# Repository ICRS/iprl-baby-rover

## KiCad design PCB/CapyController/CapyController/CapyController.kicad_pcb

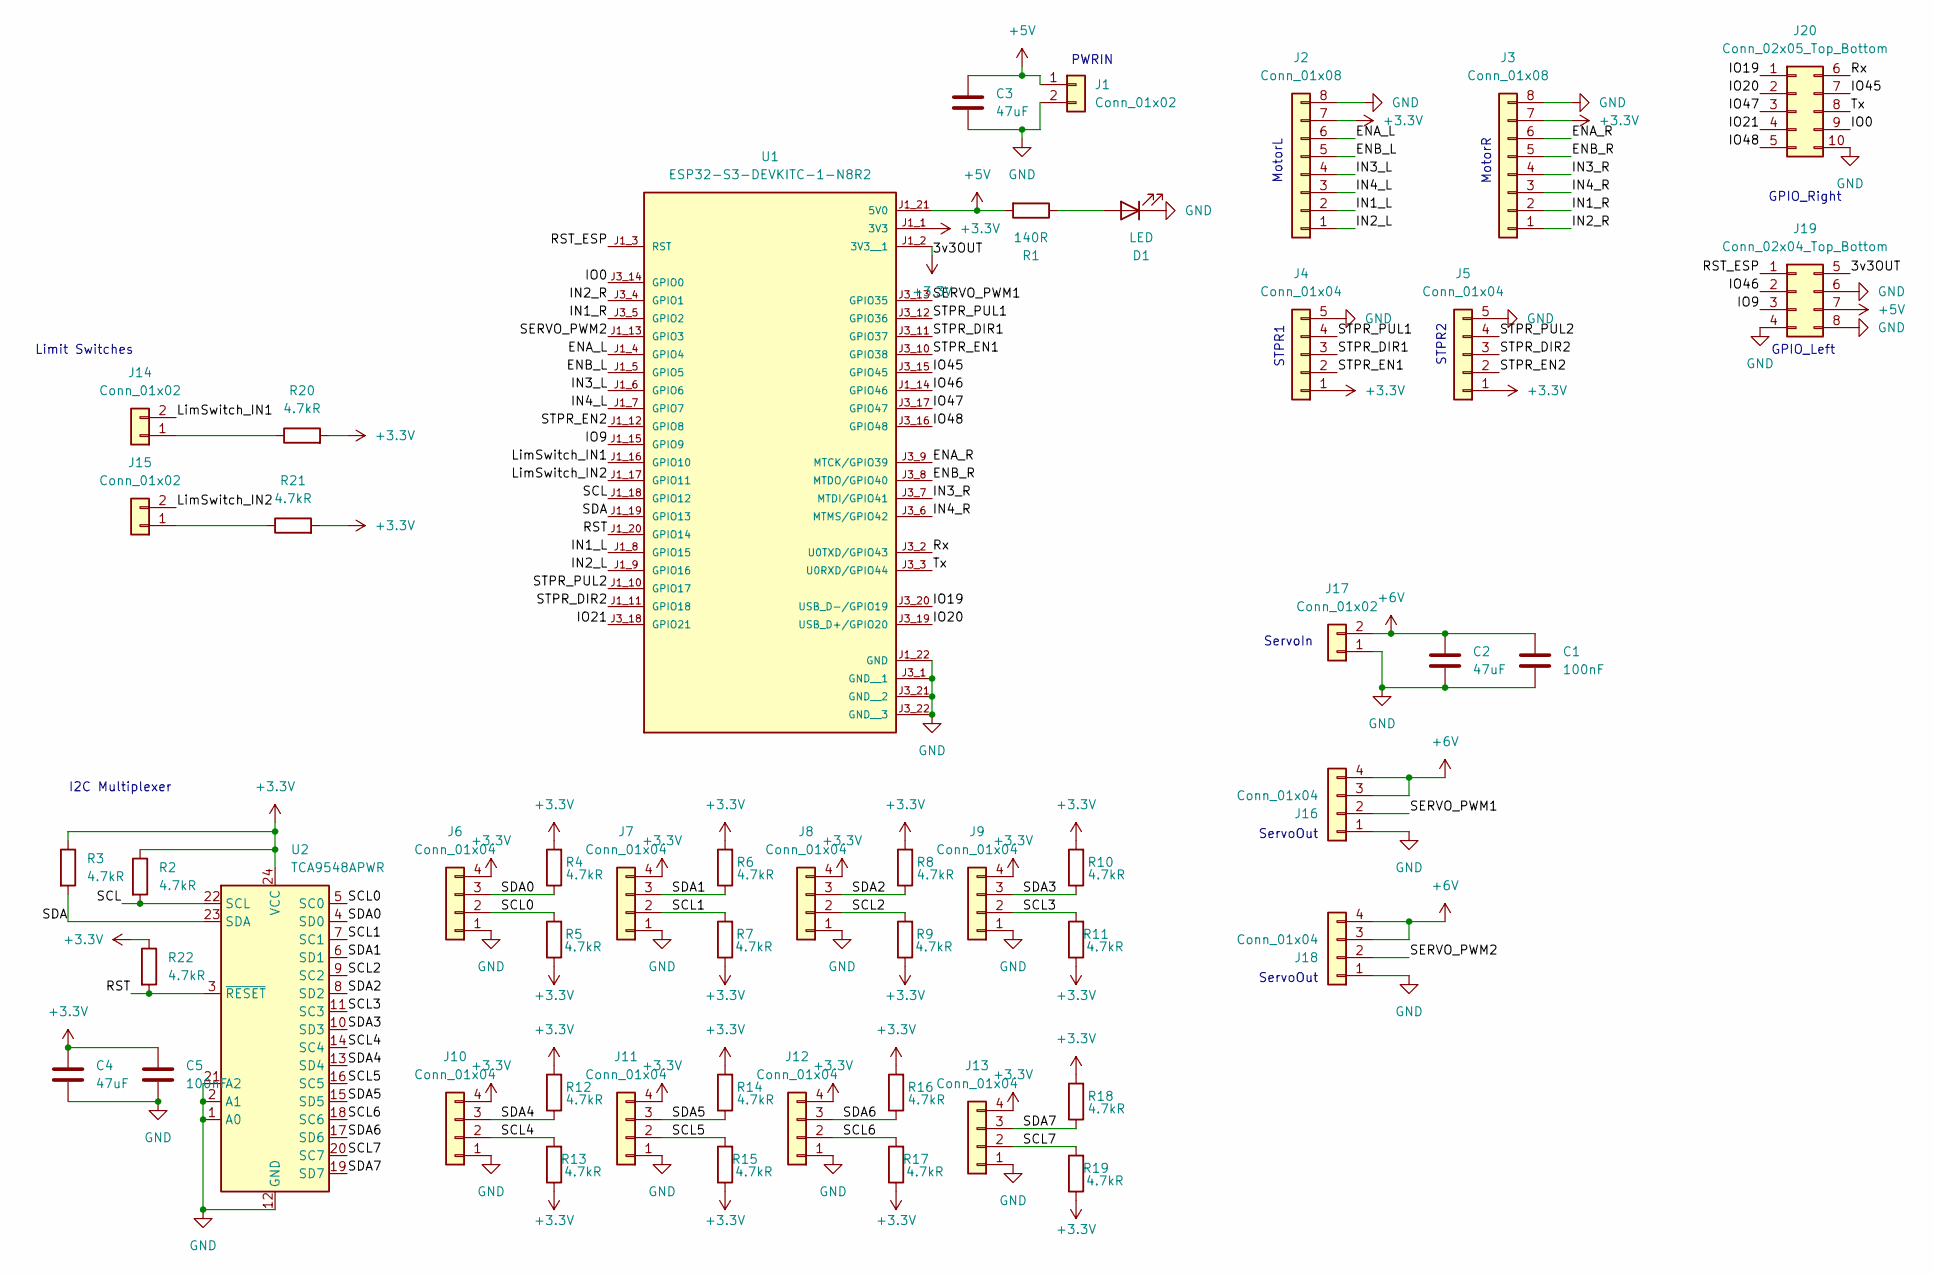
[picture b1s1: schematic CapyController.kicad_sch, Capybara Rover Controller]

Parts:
C1, C5: 100nF; C_1206_3216Metric
C2, C3, C4: 47uF; C_1206_3216Metric
D1: LED; LED_0402_1005Metric
J1, J14, J15, J17: Conn_01x02; TerminalBlock_WAGO_233-502_2x02_P2.54mm
J2, J3: Conn_01x08; JST_PH_B8B-PH-K_1x08_P2.00mm_Vertical
J4, J5: Conn_01x04; JST_PH_B5B-PH-K_1x05_P2.00mm_Vertical
J6, J7, J8, J9, J10, J11, J12, J13: Conn_01x04; JST_PH_B4B-PH-K_1x04_P2.00mm_Vertical
J16, J18: Conn_01x04; TerminalBlock_WAGO_233-504_2x04_P2.54mm
J19: Conn_02x04_Top_Bottom; PinHeader_2x04_P2.54mm_Vertical
J20: Conn_02x05_Top_Bottom; PinSocket_2x05_P2.54mm_Vertical
R1: 140R; R_0402_1005Metric
R2, R3, R4, R5, R6, R7, R8, R9, R10, R11, R12, R13, R14, R15, R16, R17, R18, R19, R20, R21, R22: 4.7kR; R_0402_1005Metric
U1: ESP32-S3-DEVKITC-1-N8R2; XCVR_ESP32-S3-DEVKITC-1-N8R2; PARTREV V1
U2: TCA9548APWR; TSSOP-24_4.4x7.8mm_P0.65mm

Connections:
+3.3V: C4.2, C5.2, J2.7, J3.7, J4.1, J5.1, J6.4, J7.4, J8.4, J9.4, J10.4, J11.4, J12.4, J13.4, J19.5, R2.1, R3.1, R4.2, R5.1, R6.2, R7.1, R8.2, R9.1, R10.2, R11.1, R12.2, R13.1, R14.2, R15.1, R16.2, R17.1, R18.2, R19.1, R20.2, R21.2, R22.1, U1.J1_1 (3V3), U1.J1_2 (3V3__1), U2.24 (VCC)
+5V: C3.2, J1.1, J19.7, R1.2, U1.J1_21 (5V0)
+6V: C1.2, C2.2, J16.3, J16.4, J17.2, J18.3, J18.4
/ENA_L: J2.6, U1.J1_4 (GPIO4)
/ENA_R: J3.6, U1.J3_9 (MTCK/GPIO39)
/ENB_L: J2.5, U1.J1_5 (GPIO5)
/ENB_R: J3.5, U1.J3_8 (MTDO/GPIO40)
/IN1_L: J2.2, U1.J1_8 (GPIO15)
/IN1_R: J3.2, U1.J3_5 (GPIO2)
/IN2_L: J2.1, U1.J1_9 (GPIO16)
/IN2_R: J3.1, U1.J3_4 (GPIO1)
/IN3_L: J2.4, U1.J1_6 (GPIO6)
/IN3_R: J3.4, U1.J3_7 (MTDI/GPIO41)
/IN4_L: J2.3, U1.J1_7 (GPIO7)
/IN4_R: J3.3, U1.J3_6 (MTMS/GPIO42)
/IO0: J20.9, U1.J3_14 (GPIO0)
/IO9: J19.3, U1.J1_15 (GPIO9)
/IO19: J20.1, U1.J3_20 (USB_D-/GPIO19)
/IO20: J20.2, U1.J3_19 (USB_D+/GPIO20)
/IO21: J20.4, U1.J3_18 (GPIO21)
/IO45: J20.7, U1.J3_15 (GPIO45)
/IO46: J19.2, U1.J1_14 (GPIO46)
/IO47: J20.3, U1.J3_17 (GPIO47)
/IO48: J20.5, U1.J3_16 (GPIO48)
/LimSwitch_IN1: J14.2, U1.J1_16 (GPIO10)
/LimSwitch_IN2: J15.2, U1.J1_17 (GPIO11)
/RST: R22.2, U1.J1_20 (GPIO14), U2.3 (~RESET)
/RST_ESP: J19.1, U1.J1_3 (RST)
/Rx: J20.6, U1.J3_2 (U0TXD/GPIO43)
/SCL: R2.2, U1.J1_18 (GPIO12), U2.22 (SCL)
/SCL0: J6.2, R5.2, U2.5 (SC0)
/SCL1: J7.2, R7.2, U2.7 (SC1)
/SCL2: J8.2, R9.2, U2.9 (SC2)
/SCL3: J9.2, R11.2, U2.11 (SC3)
/SCL4: J10.2, R13.2, U2.14 (SC4)
/SCL5: J11.2, R15.2, U2.16 (SC5)
/SCL6: J12.2, R17.2, U2.18 (SC6)
/SCL7: J13.2, R19.2, U2.20 (SC7)
/SDA: R3.2, U1.J1_19 (GPIO13), U2.23 (SDA)
/SDA0: J6.3, R4.1, U2.4 (SD0)
/SDA1: J7.3, R6.1, U2.6 (SD1)
/SDA2: J8.3, R8.1, U2.8 (SD2)
/SDA3: J9.3, R10.1, U2.10 (SD3)
/SDA4: J10.3, R12.1, U2.13 (SD4)
/SDA5: J11.3, R14.1, U2.15 (SD5)
/SDA6: J12.3, R16.1, U2.17 (SD6)
/SDA7: J13.3, R18.1, U2.19 (SD7)
/SERVO_PWM1: J16.2, U1.J3_13 (GPIO35)
/SERVO_PWM2: J18.2, U1.J1_13 (GPIO3)
/STPR_DIR1: J4.3, U1.J3_11 (GPIO37)
/STPR_DIR2: J5.3, U1.J1_11 (GPIO18)
/STPR_EN1: J4.2, U1.J3_10 (GPIO38)
/STPR_EN2: J5.2, U1.J1_12 (GPIO8)
/STPR_PUL1: J4.4, U1.J3_12 (GPIO36)
/STPR_PUL2: J5.4, U1.J1_10 (GPIO17)
/Tx: J20.8, U1.J3_3 (U0RXD/GPIO44)
GND: C1.1, C2.1, C3.1, C4.1, C5.1, D1.1 (K), J1.2, J2.8, J3.8, J4.5, J5.5, J6.1, J7.1, J8.1, J9.1, J10.1, J11.1, J12.1, J13.1, J16.1, J17.1, J18.1, J19.4, J19.6, J19.8, J20.10, U1.J1_22 (GND), U1.J3_1 (GND__1), U1.J3_21 (GND__2), U1.J3_22 (GND__3), U2.1 (A0), U2.2 (A1), U2.12 (GND), U2.21 (A2)
unnamed: D1.2 (A), R1.1
unnamed: J14.1, R20.1
unnamed: J15.1, R21.1

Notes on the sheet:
I2C Multiplexer
MotorL
STPR1
ServoOut
PWRIN
GPIO_Left
GPIO_Right
STPR2
Limit Switches
MotorR
ServoIn

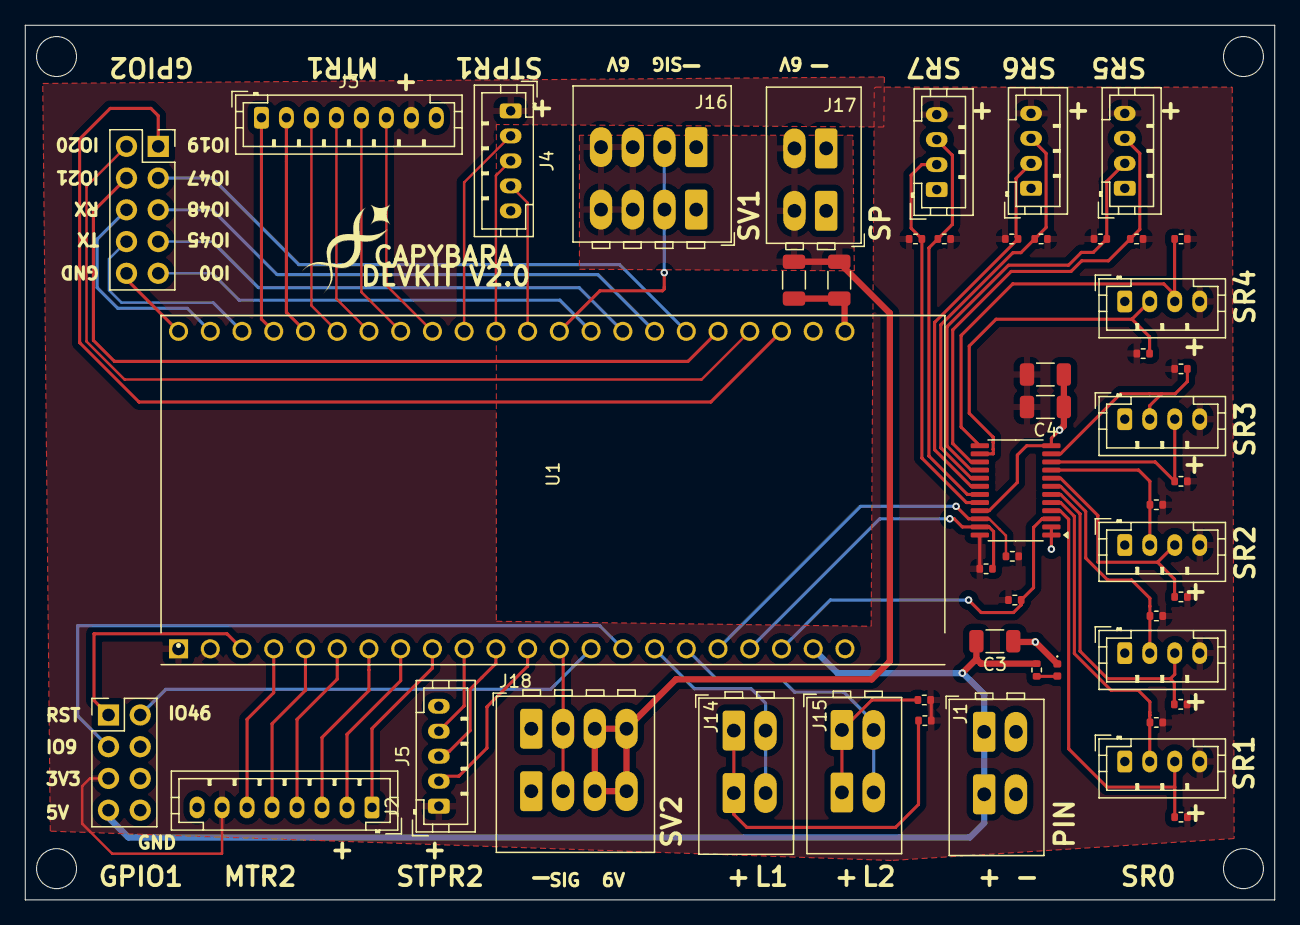
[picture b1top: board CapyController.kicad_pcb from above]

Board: 2 copper layers, 100.0 x 70.0 mm, 50 parts (0 on the bottom side), 60 nets.

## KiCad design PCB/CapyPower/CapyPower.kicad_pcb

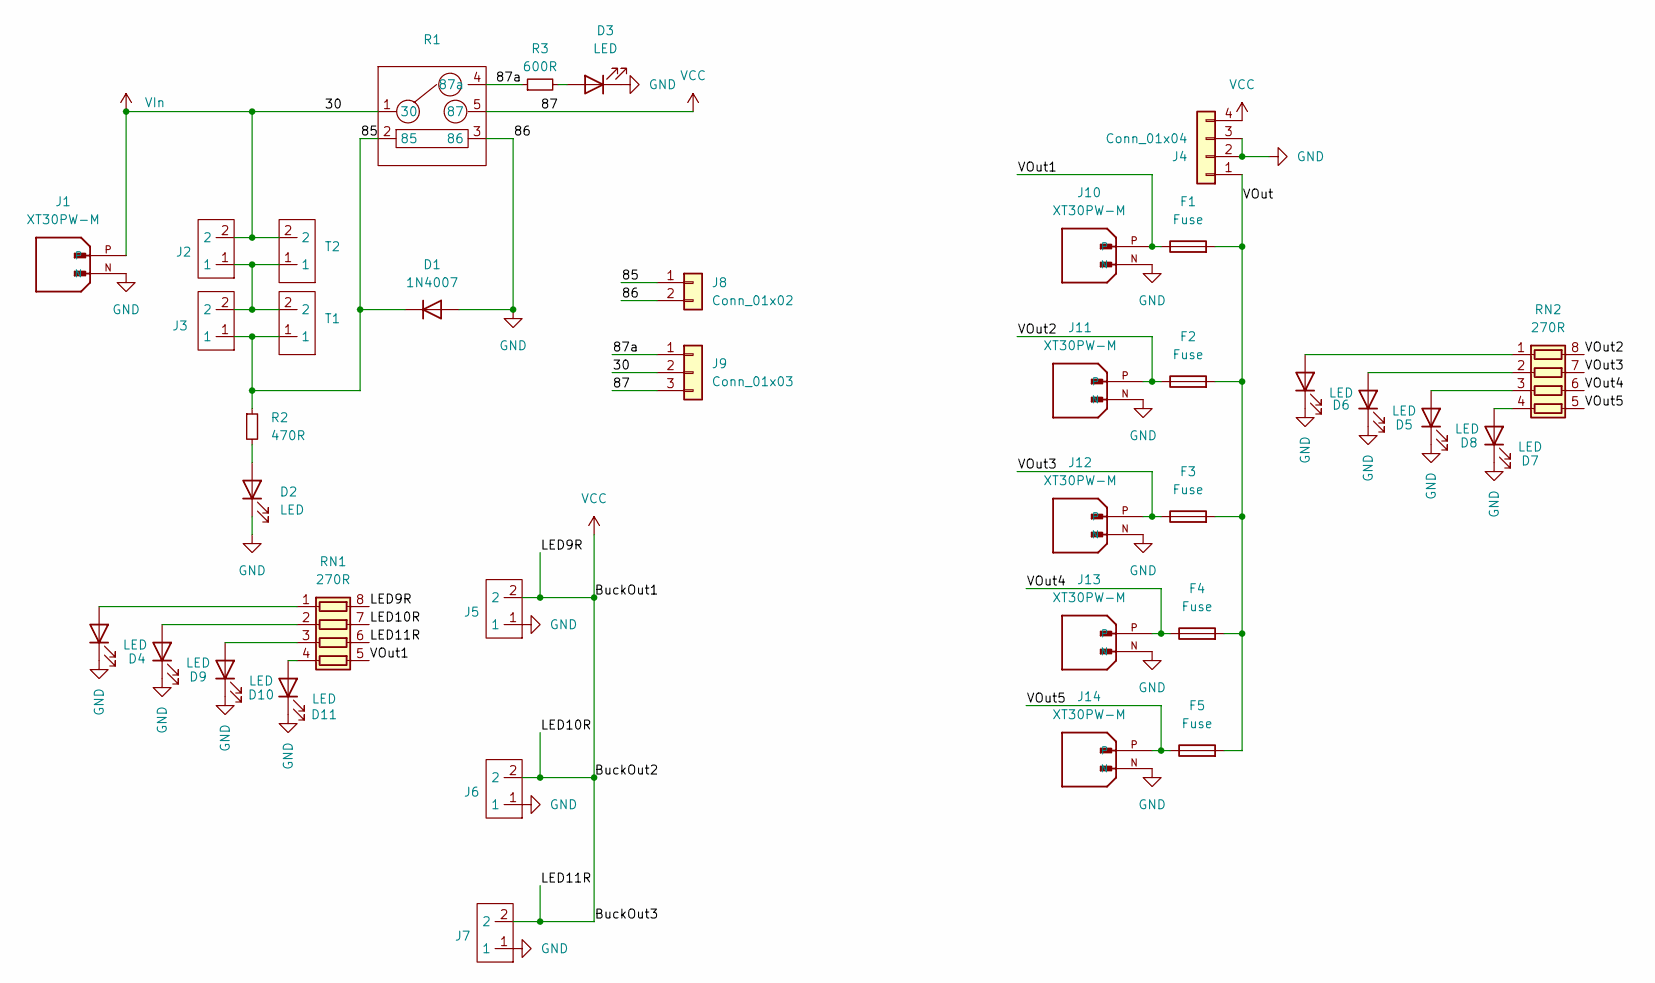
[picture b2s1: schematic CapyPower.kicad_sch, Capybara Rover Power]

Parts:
D1: 1N4007; D_DO-41_SOD81_P10.16mm_Horizontal
D2, D3, D4, D5, D6, D7, D8, D9, D10, D11: LED; LED_0402_1005Metric
F1, F2, F3, F4, F5: Fuse; Mini Blade Holder
J1, J10, J11, J12, J13, J14: XT30PW-M; AMASS_XT30PW-M; PARTREV 1.2
J2, J3, J5, J6, J7: TerminalBlock_WAGO_233-502_2x02_P2.54mm
J4: Conn_01x04; TerminalBlock_WAGO_233-504_2x04_P2.54mm
J8: Conn_01x02; ScrewTerminal_P6.00mm_2P
J9: Conn_01x03; ScrewTerminal_P6.00mm_3P
R1: CB-12V
R2: 470R; R_1206_3216Metric
R3: 600R; R_1206_3216Metric
RN1, RN2: 270R; R_Array_Convex_4x0603
T1, T2: MalePin_2.54_2P

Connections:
/85: D1.1 (K), J3.1, J8.1, R1.2 (85), R2.1, T1.1
/87a: J9.1, R1.4 (87a), R3.1
GND: D1.2 (A), D2.1 (K), D3.1 (K), D4.1 (K), D5.1 (K), D6.1 (K), D7.1 (K), D8.1 (K), D9.1 (K), D10.1 (K), D11.1 (K), J1.N, J4.2, J4.3, J5.1, J6.1, J7.1, J8.2, J10.N, J11.N, J12.N, J13.N, J14.N, R1.3 (86)
unnamed: D2.2 (A), R2.2
unnamed: D3.2 (A), R3.2
unnamed: D4.2 (A), RN1.1 (R1.1)
unnamed: D5.2 (A), RN2.2 (R2.1)
unnamed: D6.2 (A), RN2.1 (R1.1)
unnamed: D7.2 (A), RN2.4 (R4.1)
unnamed: D8.2 (A), RN2.3 (R3.1)
unnamed: D9.2 (A), RN1.2 (R2.1)
unnamed: D10.2 (A), RN1.3 (R3.1)
unnamed: D11.2 (A), RN1.4 (R4.1)
unnamed: J2.1, J3.2, T1.2, T2.1
VCC: J4.4, J5.2, J6.2, J7.2, J9.3, R1.5 (87), RN1.6 (R3.2), RN1.7 (R2.2), RN1.8 (R1.2)
VIn: J1.P, J2.2, J9.2, R1.1 (30), T2.2

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
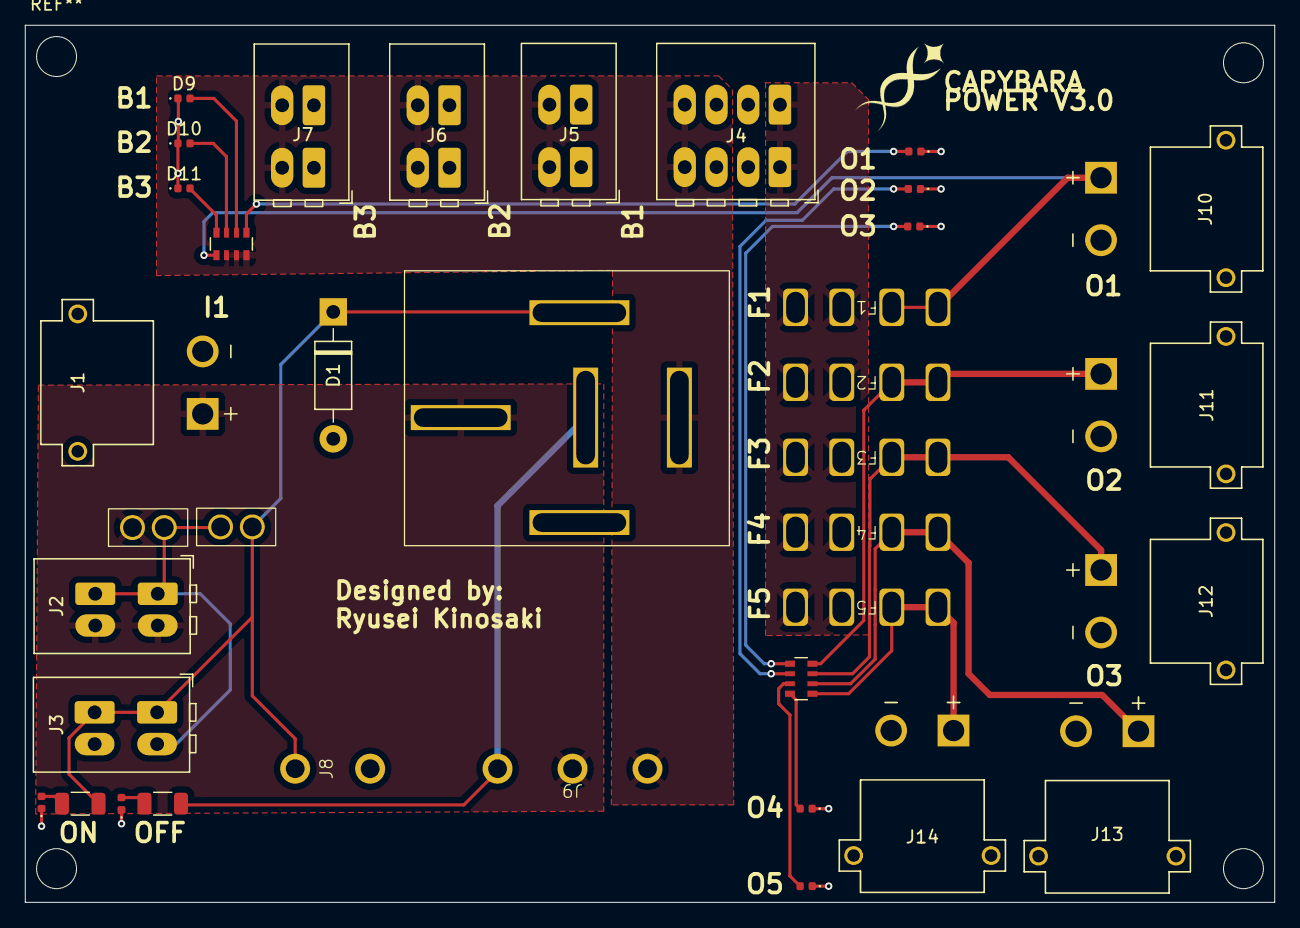
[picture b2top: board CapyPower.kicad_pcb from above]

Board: 2 copper layers, 100.0 x 70.2 mm, 37 parts (0 on the bottom side), 22 nets.

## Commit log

2025-03-23 Added PIO codebase
2025-04-02 Added PowerPCB file
2025-04-02 Added CapyPower v3.1
2025-04-02 Updated schematic name
2025-04-03 Added CapyController PCB
2025-04-09 Updated Both PCBs
2025-04-21 Updated CapyPower
2025-04-21 Updated CapyController
